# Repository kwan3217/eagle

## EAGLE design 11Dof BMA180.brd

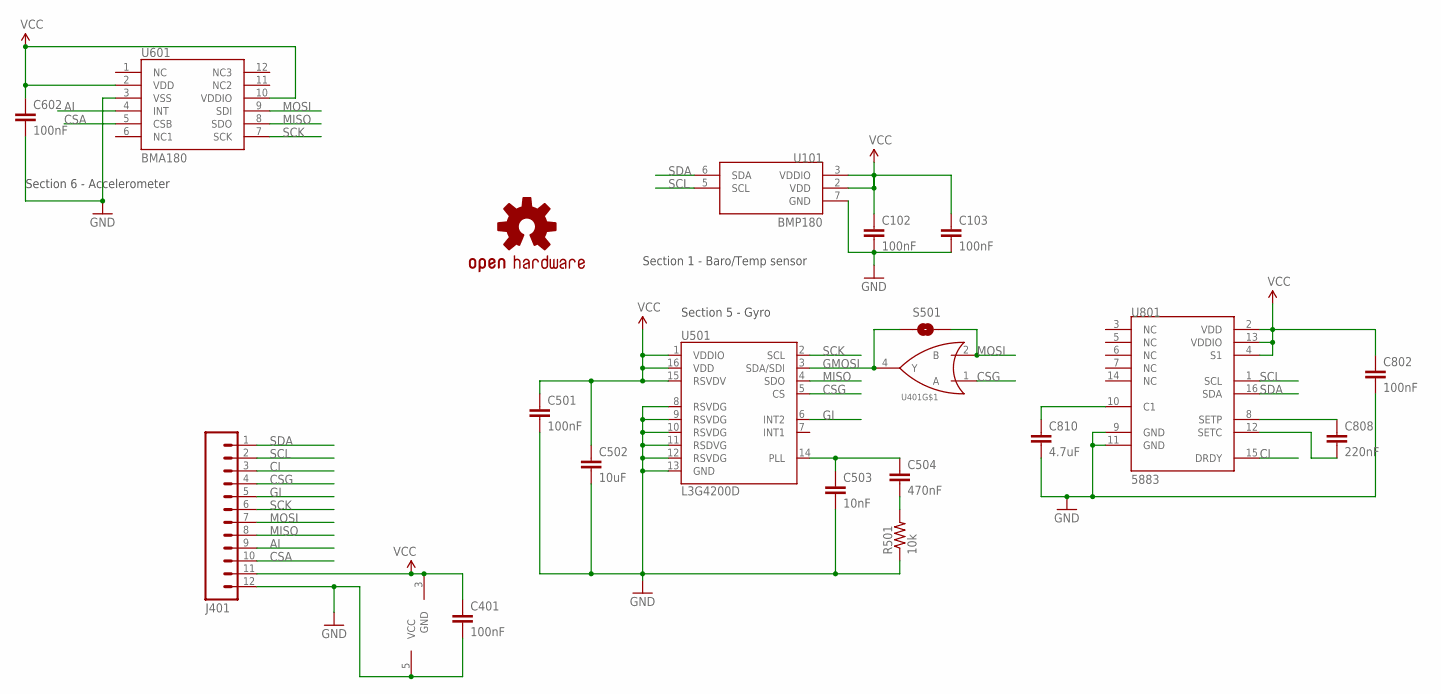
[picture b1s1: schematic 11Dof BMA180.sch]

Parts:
C102, C103, C401, C501, C602, C802: 100nF; 0603-CAP; DIGIKEY 445-1316-1-ND
C502: 10uF; 0603-CAP; DIGIKEY 445-7486-1-ND
C503: 10nF; 0603-CAP; DIGIKEY 445-1311-1-ND
C504: 470nF; 0603-CAP; DIGIKEY 445-5192-1-ND
C808: 220nF; 0603-CAP; DIGIKEY 445-5132-1-ND
C810: 4.7uF; 0603-CAP; DIGIKEY 445-7483-1-ND
J401: M12PTH; 1X12; DIGIKEY $NOPART
R501: 10k; 0603-RES; DIGIKEY P10.0KHCT-ND
S501: SOLDERJUMPERNO; SJ_2S-NO; DIGIKEY $NOPART
U101: BMP180; DIGIKEY 828-1027-1-ND
U401: SN74LVC1G32; SOT-23-5; DIGIKEY 296-9847-2-ND
U501: L3G4200D; LGA16-4X4; DIGIKEY 497-11071-1-ND
U601: BMA180; LGA12; DIGIKEY $NOPART
U801: 5883; 16LPCC; DIGIKEY 342-1082-1-ND
U$2: OSHW-LOGOS; OSHW-LOGO-S; DIGIKEY $NOPART

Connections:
AI: J401.9, U601.4 (INT)
CI: J401.3, U801.15 (DRDY)
CSA: J401.10, U601.5 (CSB)
CSG: J401.4, U401.1 (A), U501.5 (CS)
GI: J401.5, U501.6 (INT2)
GMOSI: S501.1, U401.4 (Y), U501.3 (SDA/SDI)
GND: C102.2, C103.2, C401.2, C501.2, C502.2, C503.2, C602.2, C802.2, C810.2, J401.12, R501.1, U101.7 (GND), U401.5 (VCC), U501.8 (RSVDG), U501.9 (RSVDG), U501.10 (RSVDG), U501.11 (RSDVG), U501.12 (RSVDG), U501.13 (GND), U601.3 (VSS), U801.9 (GND), U801.11 (GND)
MISO: J401.8, U501.4 (SDO), U601.8 (SDO)
MOSI: J401.7, S501.2, U401.2 (B), U601.9 (SDI)
unnamed: C503.1, C504.1, U501.14 (PLL)
unnamed: C504.2, R501.2
unnamed: C808.1, U801.8 (SETP)
unnamed: C808.2, U801.12 (SETC)
unnamed: C810.1, U801.10 (C1)
SCK: J401.6, U501.2 (SCL), U601.7 (SCK)
SCL: J401.2, U101.5 (SCL), U801.1 (SCL)
SDA: J401.1, U101.6 (SDA), U801.16 (SDA)
VCC: C102.1, C103.1, C401.1, C501.1, C502.1, C602.1, C802.1, J401.11, U101.2 (VDD), U101.3 (VDDIO), U401.3 (GND), U501.1 (VDDIO), U501.15 (RSVDV), U501.16 (VDD), U601.2 (VDD), U601.10 (VDDIO), U801.2 (VDD), U801.4 (S1), U801.13 (VDDIO)

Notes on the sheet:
Section 5 - Gyro
Section 6 - Accelerometer
Section 1 - Baro/Temp sensor

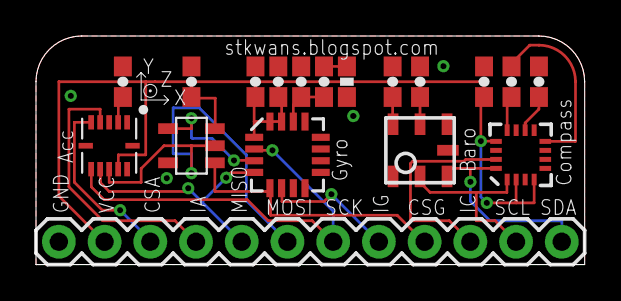
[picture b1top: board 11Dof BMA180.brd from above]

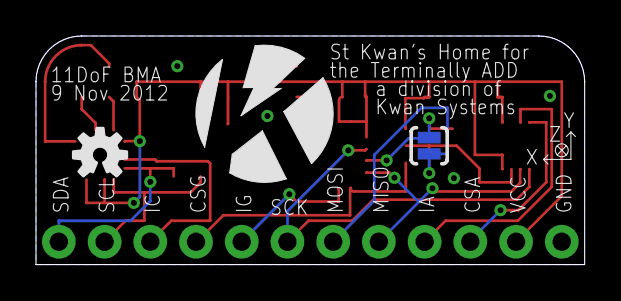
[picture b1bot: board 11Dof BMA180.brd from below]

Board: 2 copper layers, 30.5 x 12.7 mm, 21 parts (3 on the bottom side), 18 nets.

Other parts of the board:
U$1: KWAN_CIRCLE

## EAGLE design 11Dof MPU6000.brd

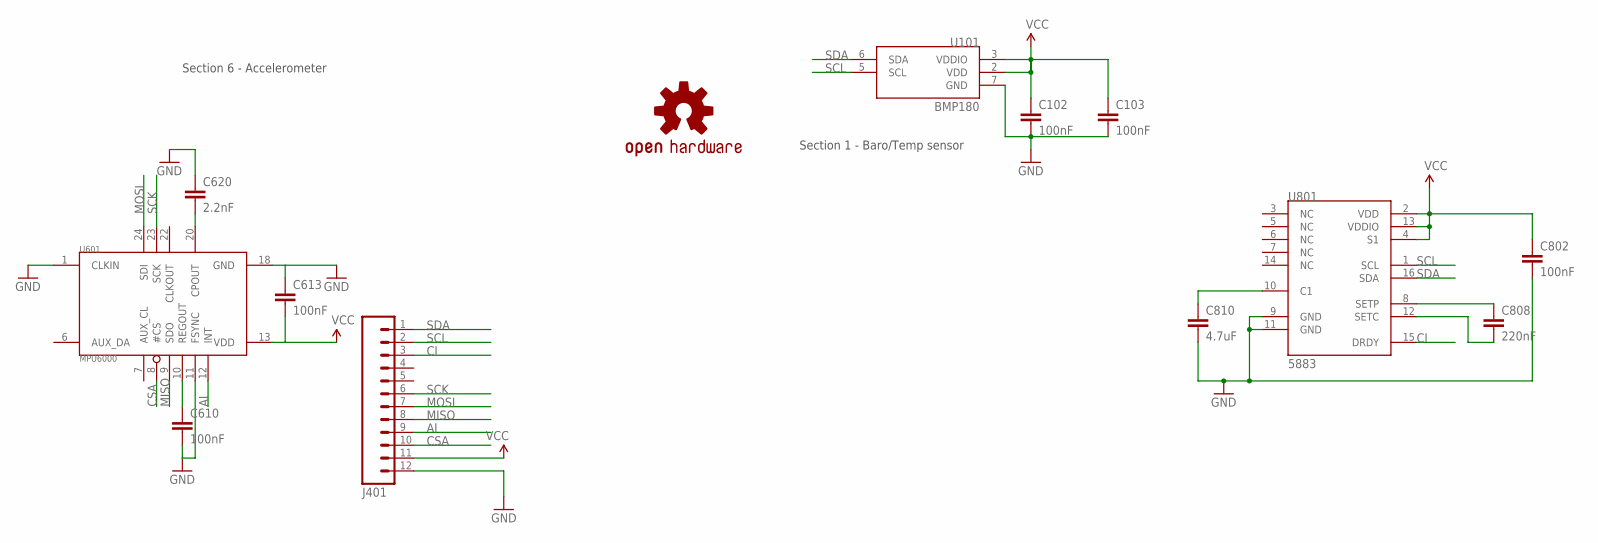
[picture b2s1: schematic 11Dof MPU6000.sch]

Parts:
C102, C103, C610, C613, C802: 100nF; 0603-CAP; DIGIKEY 445-1316-1-ND
C620: 2.2nF; 0603-CAP; DIGIKEY 445-1311-1-ND
C808: 220nF; 0603-CAP; DIGIKEY 445-5132-1-ND
C810: 4.7uF; 0603-CAP; DIGIKEY 445-7483-1-ND
J401: M12PTH; 1X12; DIGIKEY $NOPART
U101: BMP180; DIGIKEY 828-1027-1-ND
U601: MPU6000; MPU60X0
U801: 5883; 16LPCC; DIGIKEY 342-1082-1-ND
U$2: OSHW-LOGOS; OSHW-LOGO-S; DIGIKEY $NOPART

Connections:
AI: J401.9, U601.12 (INT)
CI: J401.3, U801.15 (DRDY)
CSA: J401.10, U601.8 (#CS)
GND: C102.2, C103.2, C610.2, C613.1, C620.1, C802.2, C810.2, J401.12, U101.7 (GND), U601.1 (CLKIN), U601.11 (FSYNC), U601.18 (GND), U801.9 (GND), U801.11 (GND)
MISO: J401.8, U601.9 (SDO)
MOSI: J401.7, U601.24 (SDI)
unnamed: C610.1, U601.10 (REGOUT)
unnamed: C620.2, U601.20 (CPOUT)
unnamed: C808.1, U801.8 (SETP)
unnamed: C808.2, U801.12 (SETC)
unnamed: C810.1, U801.10 (C1)
SCK: J401.6, U601.23 (SCK)
SCL: J401.2, U101.5 (SCL), U801.1 (SCL)
SDA: J401.1, U101.6 (SDA), U801.16 (SDA)
VCC: C102.1, C103.1, C613.2, C802.1, J401.11, U101.2 (VDD), U101.3 (VDDIO), U601.13 (VDD), U801.2 (VDD), U801.4 (S1), U801.13 (VDDIO)

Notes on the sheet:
Section 6 - Accelerometer
Section 1 - Baro/Temp sensor

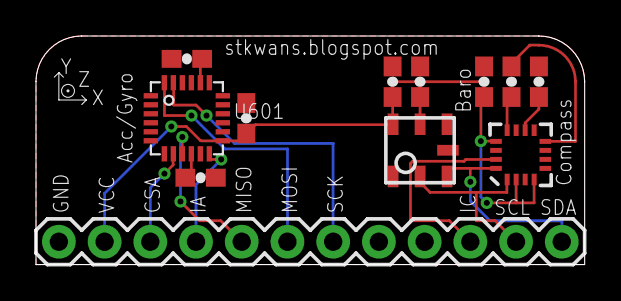
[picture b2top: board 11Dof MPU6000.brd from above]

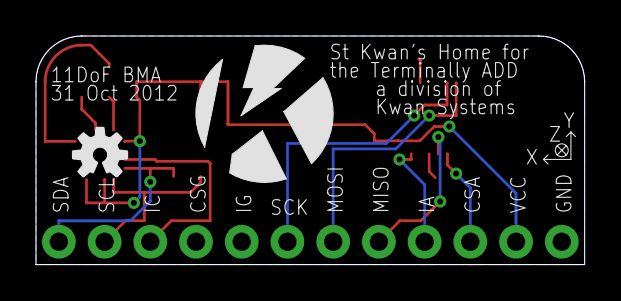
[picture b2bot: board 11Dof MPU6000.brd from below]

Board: 2 copper layers, 30.5 x 12.7 mm, 14 parts (2 on the bottom side), 15 nets.

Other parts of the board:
U$1: KWAN_CIRCLE

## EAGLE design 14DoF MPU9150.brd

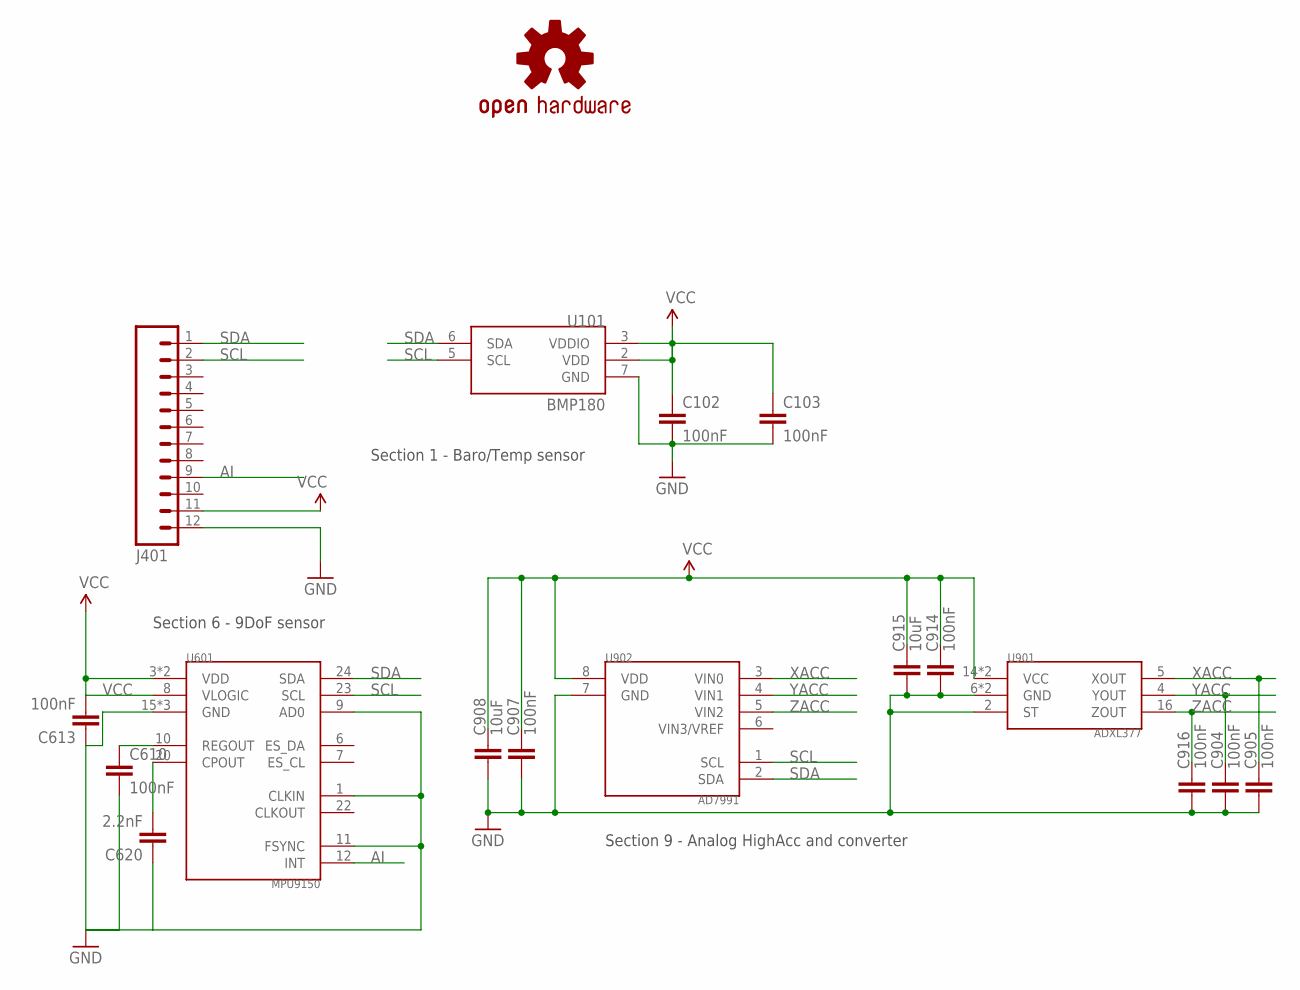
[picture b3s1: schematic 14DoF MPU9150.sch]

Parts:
C102, C103, C610, C613, C904, C905, C907, C914, C916: 100nF; 0603-CAP; DIGIKEY 445-1317-2-ND
C620: 2.2nF; 0603-CAP; DIGIKEY 445-1309-2-ND
C908, C915: 10uF; 0603-CAP; DIGIKEY 445-7486-1-ND
J401: M12PTH; 1X12; DIGIKEY $NOPART
U101: BMP180; DIGIKEY 828-1027-1-ND
U601: MPU9150; LLGA24
U901: ADXL377; DIGIKEY ADXL377BCPZ-RL7CT-ND
U902: AD7991; SOT-23-8; DIGIKEY AD7991YRJZ-0500RL7CT-ND
U$2: OSHW-LOGOS; OSHW-LOGO-S; DIGIKEY $NOPART

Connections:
AI: J401.9, U601.12 (INT)
GND: C102.2, C103.2, C610.2, C613.1, C620.1, C904.2, C905.2, C907.2, C908.2, C914.2, C915.2, C916.2, J401.12, U101.7 (GND), U601.1 (CLKIN), U601.9 (AD0), U601.11 (FSYNC), U601.15 (GND), U601.17 (GND), U601.18 (GND), U901.2 (ST), U901.6 (GND), U901.7 (GND), U902.7 (GND)
unnamed: C610.1, U601.10 (REGOUT)
unnamed: C620.2, U601.20 (CPOUT)
SCL: J401.2, U101.5 (SCL), U601.23 (SCL), U902.1 (SCL)
SDA: J401.1, U101.6 (SDA), U601.24 (SDA), U902.2 (SDA)
VCC: C102.1, C103.1, C613.2, C907.1, C908.1, C914.1, C915.1, J401.11, U101.2 (VDD), U101.3 (VDDIO), U601.3 (VDD), U601.8 (VLOGIC), U601.13 (VDD), U901.14 (VCC), U901.15 (VCC), U902.8 (VDD)
XACC: C905.1, U901.5 (XOUT), U902.3 (VIN0)
YACC: C904.1, U901.4 (YOUT), U902.4 (VIN1)
ZACC: C916.1, U901.16 (ZOUT), U902.5 (VIN2)

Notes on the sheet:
Section 6 - 9DoF sensor
Section 1 - Baro/Temp sensor
Section 9 - Analog HighAcc and converter

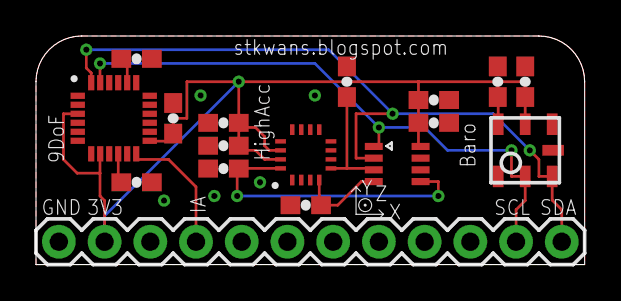
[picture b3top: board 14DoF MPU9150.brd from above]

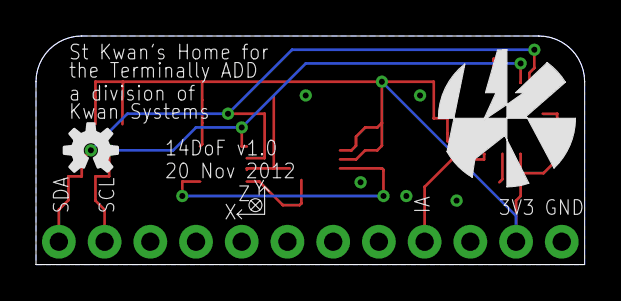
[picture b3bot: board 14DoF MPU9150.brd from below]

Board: 2 copper layers, 30.5 x 12.7 mm, 20 parts (2 on the bottom side), 10 nets.

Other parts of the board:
U$1: KWAN_ACC
U$3: AXES_SM
